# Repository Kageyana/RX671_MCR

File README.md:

# 初期設定
1. ワークスペースのパスは2バイト文字禁止
2. e2studio プロジェクトの設定→C/C++ビルド→設定<br>ツール設定タブ→Compiler→Includesに<br>
```"${workspace_loc:/${ProjName}/inc}"```<br>
を追加
3. Renesas Extensions for Visual Studio Codeを使う場合<br>
	1. 下記ページを参考に拡張機能をインストールする
	https://qiita.com/y_toyoyama/items/98b7511f9f95343f7a40<br>
	2. launch.json<br>
	serverParametersはデバッガ情報をLLMに渡して整形してもらうと楽
	3. CMakeLists.txt<br>
	CMAKE_CURRENT_SOURCE_DIRに```"inc/*.h"```を追加<br>
	CMAKE_CXX_FLAGSにコンパイラオプションを追加する<br>
	CMAKE_EXE_LINKER_FLAGSにリンカオプションを追加する
	4. .clangd<br>
	下記リポジトリを参考に.clangdとc_cpp_intellisense_helper.hを追加する<br>
	https://github.com/NoMaY-jp/Renesas_VSCode_Extensions_tips_for_Renesas_CC_compilers.git

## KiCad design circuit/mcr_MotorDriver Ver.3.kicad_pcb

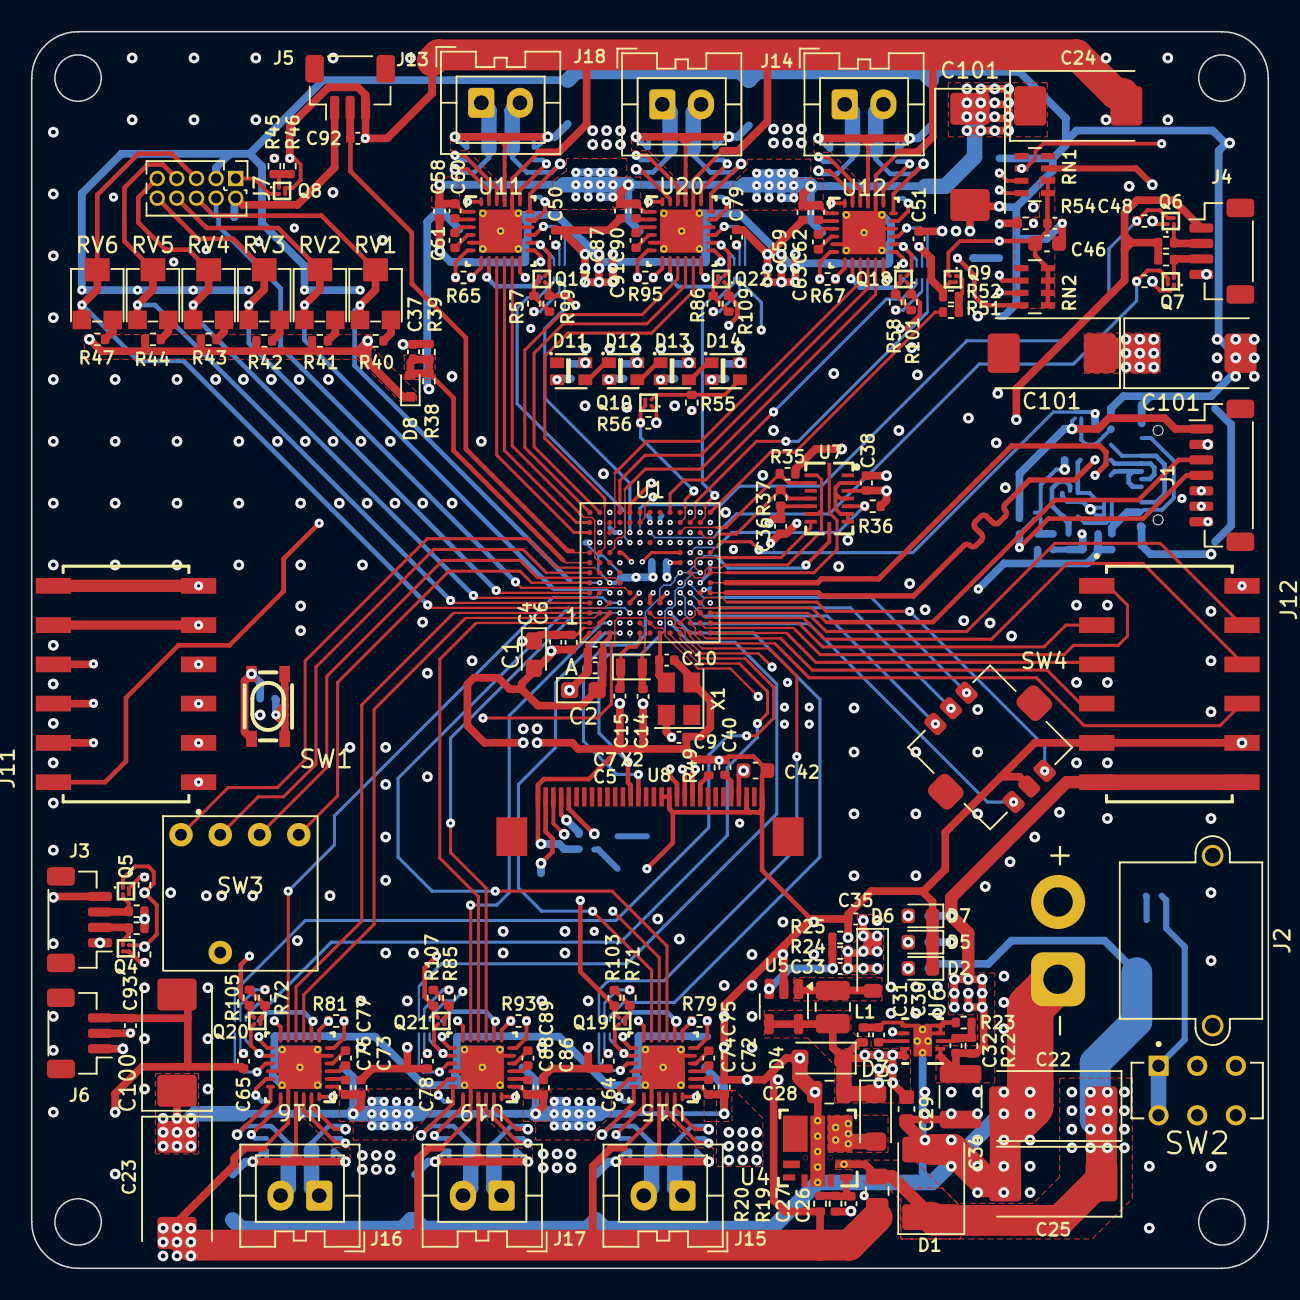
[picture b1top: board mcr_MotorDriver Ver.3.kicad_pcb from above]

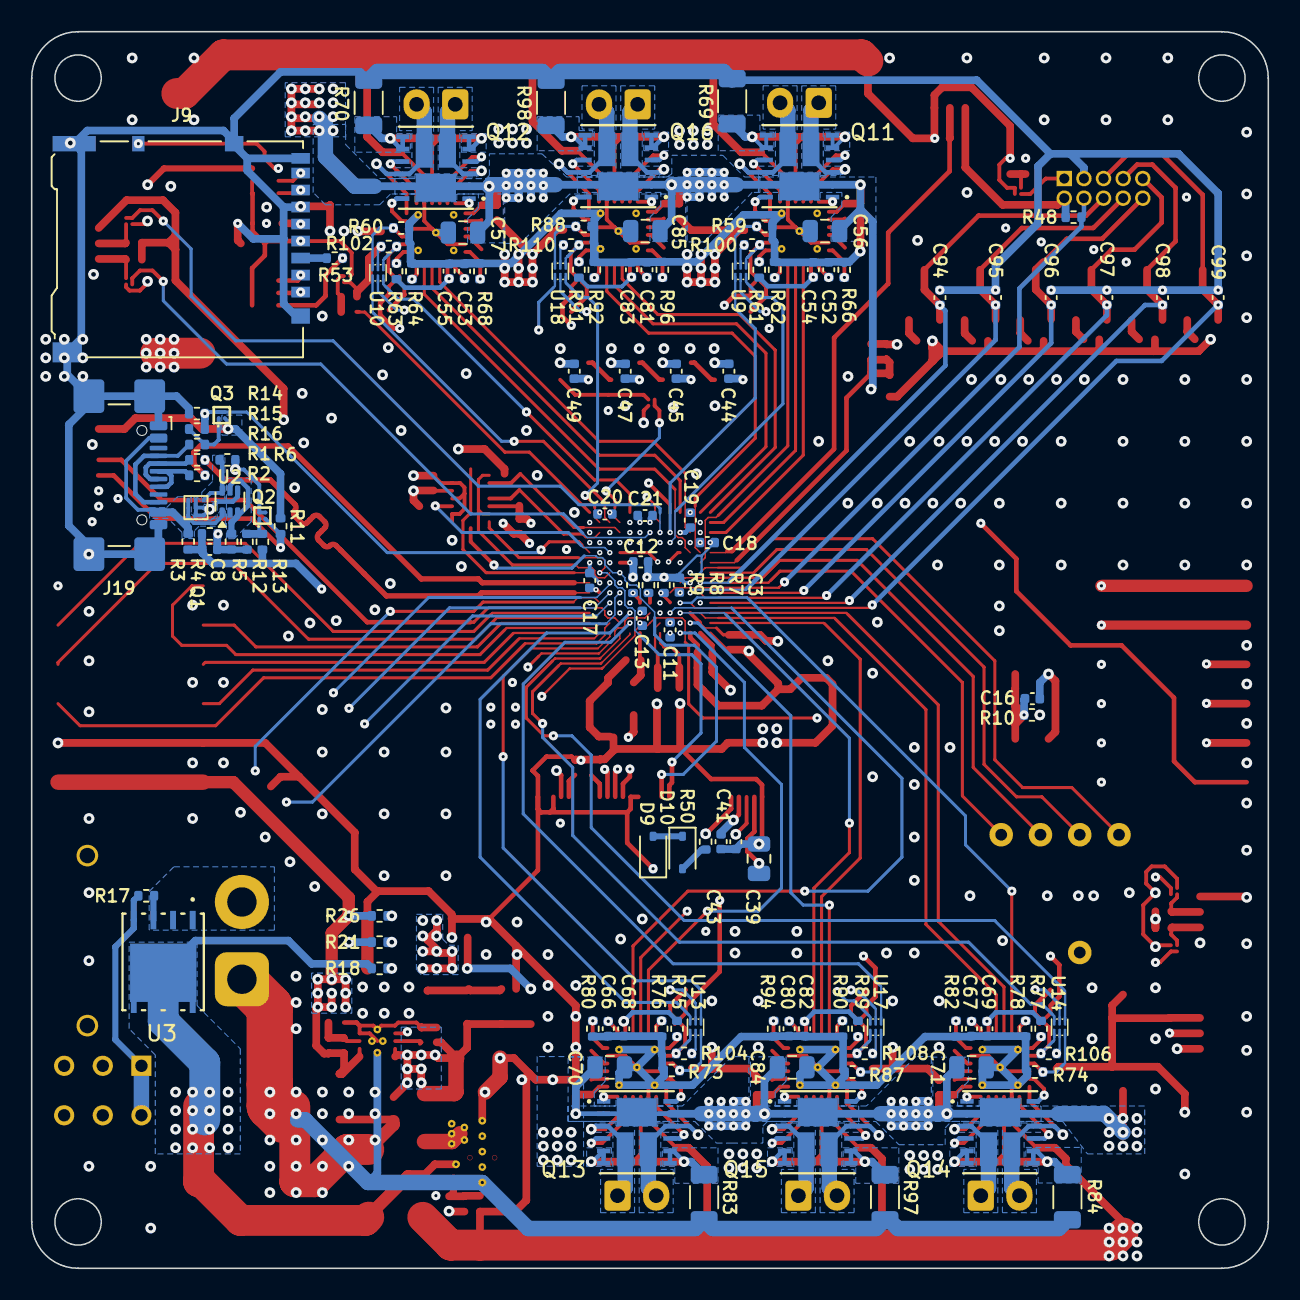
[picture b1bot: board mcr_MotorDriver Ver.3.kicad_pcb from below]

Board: 6 copper layers, 80.0 x 80.0 mm, 301 parts (122 on the bottom side), 268 nets.

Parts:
C1, C2: 10u; CP_EIA-2012-12_Kemet-R
C3, C4, C5, C12, C13, C17, C18, C19, C20, C21, C36, C37, C38, C44, C45, C47, C48, C49, C50, C51, C58, C59, C61, C63, C64, C65, C72, C73, C75, C77, C78, C79, C86, C87, C89, C91: 0.1u; C_0402_1005Metric
C6, C7, C9: 0.01u; C_0402_1005Metric
C8, C40, C41, C43, C52, C53, C54, C55, C60, C62, C66, C67, C68, C69, C74, C76, C80, C81, C82, C83, C88, C90: 1u; C_0402_1005Metric
C10: 15p; C_0402_1005Metric
C11: 0.22u; C_0402_1005Metric
C14, C15, C16: 12p; C_0402_1005Metric
C22, C23, C24, C25, C100, C101, C101#2, C101#3: 150u; CP_EIA-7343-31_Kemet-D
C26, C39, C56, C57, C70, C71, C84, C85: 10u; C_0805_2012Metric
C27: 330p; C_0402_1005Metric
C28: 47u; C_0805_2012Metric
C29, C42, C46: 10u; C_0603_1608Metric
C30: 100n; C_0402_1005Metric
C31: 2.2u; C_0402_1005Metric
C32: 10n; C_0402_1005Metric
C33: 160p; C_0402_1005Metric
C34: 22u; C_1210_3225Metric
C35: 4.7u; C_0402_1005Metric
C92, C93, C94, C95, C96, C97, C98, C99: 1000p; C_0402_1005Metric
D1: 1SMB5931BT3G; D_2114_3652Metric
D2: Red; LED_0603_1608Metric
D3: D_Schottky; D_SOD-123W
D4: KDZVTR6.2B; D_SOD-123F
D5: Yellow; LED_0603_1608Metric
D6: MBR0520; D_SOD-123
D7: Green; LED_0603_1608Metric
D8: BAT30KFILM; D_SOD-523
D9, D10: 1N4148WS; D_SOD-323
D11, D12, D13, D14: WS2812C; WS2812C-2020
J1: SH_01x07; JST_SH_BM07B-SRSS-TB_1x07-1MP_P1.00mm_Vertical
J2: XT30; AMASS_XT30PW-M_1x02_P2.50mm_Horizontal
J3, J4: SH_01x04; JST_SH_BM04B-SRSS-TB_1x04-1MP_P1.00mm_Vertical
J5, J6: SH_01x03; JST_SH_BM03B-SRSS-TB_1x03-1MP_P1.00mm_Vertical
J7: Conn_02x05; FTSH-105-01-F-D-K
J9: Micro_SD_Card_Det_Hirose_DM3AT; microSD_HC_Hirose_DM3AT-SF-PEJM5
J11: Pmod12P_UART; Pmod_2x06_P2.54mm
J12: Pmod12P_SPI; Pmod_2x06_P2.54mm
J13, J14, J15, J16, J17, J18: motor1; JST_XA_B02B-XASK-1_1x02_P2.50mm_Vertical
J19: USB_C_Receptacle_USB2.0_14P; USB_C_Receptacle_GCT_USB4110
L1: 10uH; L_1008_2520Metric
Q1: DMP1011UCB9-7
Q2, Q3, Q4, Q5, Q6, Q7, Q8, Q10, Q17, Q18, Q19, Q20, Q21, Q22: DMN1054UCB4
Q9: DMP1100UCB4-7; DMN1054UCB4
Q11, Q12, Q13, Q14, Q15, Q16: DMHT6016LFJ; V-DFN5045-12_DIO
R1, R2: 27; R_0402_1005Metric
R3: 15k; R_0402_1005Metric
R4, R18: 30k; R_0402_1005Metric
R5, R6: 12.1k; R_0402_1005Metric
R7, R8, R9, R10, R19, R59, R60, R61, R63, R73, R74, R75, R77, R87, R88, R89, R91: 10k; R_0402_1005Metric
R11, R14, R27, R28, R29, R30, R31, R32, R33, R34, R35, R36, R37, R46, R55, R56, R66, R68, R80, R82, R94, R96: 4.7k; R_0402_1005Metric
R12, R15, R17, R52, R99, R100, R101, R102, R103, R104, R105, R106, R107, R108, R109, R110: 47k; R_0402_1005Metric
R13, R16, R45, R51: 330; R_0402_1005Metric
R20: 1.37k; R_0402_1005Metric
R21: 4.6k; R_0402_1005Metric
R22: 3.57k; R_0402_1005Metric
R23: 1.15k; R_0402_1005Metric
R24: 127k; R_0402_1005Metric
R25: 13.3k; R_0402_1005Metric
R26: 800; R_0402_1005Metric
R38: 62k; R_0402_1005Metric
R39: 12k; R_0402_1005Metric
R40, R41, R42, R43, R44, R47, R48: 6.2k; R_0402_1005Metric
R49: 560k; R_0402_1005Metric
R50: 50; R_0402_1005Metric
R53, R54: 22; R_0402_1005Metric
R57, R58, R71, R72, R85, R86: 1k; R_0402_1005Metric
R62, R64, R76, R78, R90, R92: 200k; R_0402_1005Metric
R65, R67, R79, R81, R93, R95: 2.2k; R_0402_1005Metric
R69, R70, R83, R84, R97, R98: 50m; R_1206_3216Metric
RN1, RN2: 22k; R_Array_Concave_4x0603
RV1, RV2, RV3, RV4, RV5, RV6: POT; ST-32EA
SW1: SW_Push; SKRPABE010
SW2: EG1271; SW_EG1271
SW3: FR01FR16P-S
SW4: SKRHAAE010
U1: R5F5671EHGLE; R5F5671EHGLE-20
U2: NSVT3906DXV6T1G; SOT-563
U3: HSBA3119; IRFH7084TRPBF_INF
U4: TPSM84209RKHT
U5: LM2733YMF; SOT-23-5
U6: TPS7A9201DSKR; TPS7A9201DSKT
U7: BMI088
U8: SSD1351
U9, U10, U13, U14, U17, U18: SN74LVC1G18DSFR
U11, U12, U15, U16, U19, U20: DRV8701
X1: OT322516MJBA4SL; Oscillator_SMD_Abracon_ASE-4Pin_3.2x2.5mm
X2: X1A0000610006; Crystal_SMD_2012-2Pin_2.0x1.2mm

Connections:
+3V3: C1.1, C2.1, C3.1, C4.2, C5.2, C6.2, C7.2, C9.1, C12.1, C13.1, C17.1, C18.2, C19.2, C20.1, C21.1, C32.2, C34.2, C36.1, C38.1, C42.2, C43.2, C50.2, C51.2, C64.2, C65.2, C78.2, C79.2, D8.1 (K), J1.1, J5.1, J6.1, J7.2, J11.6, J11.12, J12.6, J12.12, Q3.3 (D), Q4.1 (G), Q5.1 (G), Q6.1 (G), Q7.1 (G), Q9.2 (S), Q10.1 (G), R9.1, R10.2, R11.2, R22.2, R26.2, R27.2, R28.2, R29.2, R30.2, R35.1, R36.2, R37.2, R40.1, R41.1, R42.1, R43.1, R44.1, R47.1, R48.1, R52.2, R56.2, R100.2, R102.2, R104.2, R106.2, R108.2, R110.2, RN1.7 (R2.2), U1.B1 (AVCC1), U1.B2 (AVCC0), U1.B10 (VCC), U1.C3 (VREFH0), U1.D5 (VCC), U1.D11 (VCC), U1.F4 (vbatt), U1.H2 (VCC), U1.H12 (VCC_USB), U1.K8 (VCC), U1.M5 (VCC_USB), U1.M13 (VCC), U6.1 (OUT), U6.2 (OUT), U7.3 (VDD), U7.11 (VDDIO), U8.4 (VDDIO), U8.27 (VCI), U9.5 (Vcc), U10.5 (Vcc), U13.5 (Vcc), U14.5 (Vcc), U17.5 (Vcc), U18.5 (Vcc), X1.4 (Vdd)
+5V: C27.2, C28.2, C29.2, C31.2, C44.2, C45.2, C47.2, C49.2, D3.1 (K), D4.1 (K), D11.4 (VDD), D12.4 (VDD), D13.4 (VDD), D14.4 (VDD), J3.1, J4.1, L1.1, Q1.2 (S), R19.2, R21.2, R31.2, R32.2, R33.2, R34.2, R55.2, U2.4 (E1), U5.4 (EN), U5.5 (VIN), U6.7 (EN), U6.9 (IN), U6.10 (IN)
+13V: C33.2, C35.2, C39.2, D6.1 (K), R24.2, U8.2 (VCC)
+BATT: C22.1, C23.1, C24.1, C25.1, C26.2, C56.1, C57.1, C58.1, C59.1, C60.1, C62.1, C70.1, C71.1, C72.1, C73.1, C74.1, C76.1, C84.1, C85.1, C86.1, C87.1, C88.1, C90.1, C100.1, C101.1, C101#2.1, C101#3.1, D1.1 (K), Q11.2 (D1/D4), Q11.11 (D1/D4), Q11.13 (D1/D4), Q12.2 (D1/D4), Q12.11 (D1/D4), Q12.13 (D1/D4), Q13.2 (D1/D4), Q13.11 (D1/D4), Q13.13 (D1/D4), Q14.2 (D1/D4), Q14.11 (D1/D4), Q14.13 (D1/D4), Q15.2 (D1/D4), Q15.11 (D1/D4), Q15.13 (D1/D4), Q16.2 (D1/D4), Q16.11 (D1/D4), Q16.13 (D1/D4), R18.2, R38.2, U3.5 (D), U3.6 (D), U3.7 (D), U3.8 (D), U4.2 (VIN), U11.1 (VM), U12.1 (VM), U15.1 (VM), U16.1 (VM), U19.1 (VM), U20.1 (VM)
/MCU/AN001: C99.2, J7.5, RV6.2, RV6.3, U1.C4 (P41)
/MCU/AN002: C98.2, J7.7, RV5.2, RV5.3, U1.A4 (P42)
/MCU/AN003: C97.2, J7.9, RV4.2, RV4.3, U1.B5 (P43)
/MCU/AN004: J7.4, R48.2, U1.E5 (P44)
/MCU/AN005: C96.2, J7.10, RV3.2, RV3.3, U1.A5 (P45)
/MCU/AN006: C95.2, J7.8, RV2.2, RV2.3, U1.C5 (P46)
/MCU/AN007: C94.2, J7.6, RV1.2, RV1.3, U1.B6 (P47)
/MCU/AN100: U1.C9 (PD7), U12.11 (SO)
/MCU/AN101: C92.2, J5.2, U1.A9 (PD6)
/MCU/AN103: U1.B9 (PD4), U20.11 (SO)
/MCU/AN105: C37.2, D8.2 (A), R38.1, R39.2, U1.A8 (PD2)
/MCU/AN106: C93.2, J6.2, U1.C7 (PD1)
/MCU/AN107: U1.B8 (PD0), U11.11 (SO)
/MCU/AN109: U1.C2 (P02), U19.11 (SO)
/MCU/AN110: U1.D4 (P01), U16.11 (SO)
/MCU/AN111: U1.D1 (P00), U15.11 (SO)
/MCU/EXTAL: C10.2, U1.H1 (EXTAL), X1.3 (OUT)
/MCU/IRQ10: U1.N7 (P55), U7.16 (INT1)
/MCU/IRQ14: R37.1, U1.M11 (PC0), U7.12 (INT3)
/MCU/MD: J1.4, Q2.3 (D), R11.1, U1.G3 (md/fined)
/MCU/MTIOC0A: U1.J1 (P34), U14.3 (A)
/MCU/MTIOC0C: U1.J3 (P32), U13.3 (A)
/MCU/MTIOC3A: U1.M12 (PC1), U18.3 (A)
/MCU/MTIOC3C: U1.F3 (pj3), U17.3 (A)
/MCU/MTIOC4A: U1.E10 (PA0), U9.3 (A)
/MCU/MTIOC4C: U1.J13 (PB1), U10.3 (A)
/MCU/MTIOC7C: R45.1, U1.E13 (P67)
/MCU/MTLCKA: Q6.2 (S), R29.1, U1.F11 (PA4)
/MCU/MTLCKB: Q7.2 (S), R30.1, U1.G11 (PA6)
/MCU/MTLCKC: Q5.2 (S), R28.1, U1.F12 (PA1)
/MCU/MTLCKD: Q4.2 (S), R27.1, U1.F10 (PA3)
/MCU/P03: U1.D3 (P03), U19.9 (FAULT_N)
/MCU/P05: U1.B3 (P05), U16.9 (FAULT_N)
/MCU/P07: U1.A2 (P07), U19.10 (SNSOUT)
/MCU/P12: SW4.4, U1.M4 (P12)
/MCU/P13: SW4.2, U1.L5 (P13)
/MCU/P14: Q21.1 (G), R107.1, U1.N4 (P14)
/MCU/P15: Q20.1 (G), R105.1, U1.K4 (P15)
/MCU/P17(CS): J12.1, U1.M2 (P17)
/MCU/P20(MOSI): J12.2, U1.N2 (P20)
/MCU/P21(MISO): J12.3, U1.N1 (P21)
/MCU/P22(SCK): J12.4, U1.M1 (P22)
/MCU/P23: J12.10, U1.L2 (P23)
/MCU/P24: SW4.3, U1.L4 (P24)
/MCU/P25: U1.L1 (P25), U13.1 (S)
/MCU/P27: U1.K1 (P27), U14.1 (S)
/MCU/P31(INT): J12.7, U1.K3 (P31)
/MCU/P33: U1.J2 (P33), U17.1 (S)
/MCU/P40: U1.A3 (P40), U16.10 (SNSOUT)
/MCU/P53: U1.K6 (P53*1), U8.21 (RES#)
/MCU/P54: SW4.6, U1.K5 (P54)
/MCU/P56: SW4.1, U1.L6 (P56)
/MCU/P60: U1.D8 (P60), U8.19 (CS#)
/MCU/P61: J11.10, U1.B11 (P61)
/MCU/P62: U1.A11 (P62), U11.9 (FAULT_N)
/MCU/P63: J11.9, U1.C10 (P63)
/MCU/P64: U1.D9 (P64), U8.20 (D/C#)
/MCU/P66: U1.E11 (P66), U9.1 (S)
/MCU/P73: U1.L12 (P73), U10.1 (S)
/MCU/P74: R51.2, U1.N13 (P74)
/MCU/P80(RTS): J11.4, U1.K9 (P80)
/MCU/P82(TXD): J11.2, U1.N10 (P82)
/MCU/P83(CTS): J11.1, U1.L8 (P83)
/MCU/P86: J12.9, U1.M3 (P86)
/MCU/P87(RESET): J12.8, U1.N3 (P87)
/MCU/P90: SW3.8, U1.A6 (P90)
/MCU/P91: SW3.1, U1.B7 (P91)
/MCU/P92: SW3.2, U1.A7 (P92)
/MCU/P93: SW3.4, U1.D6 (P93)
/MCU/PA7: Q17.1 (G), R99.1, U1.H11 (PA7)
/MCU/PB0: U1.H10 (PB0), U18.1 (S)
/MCU/PB2: Q22.1 (G), R109.1, U1.J12 (PB2)
/MCU/PB3: Q19.1 (G), R103.1, U1.J10 (PB3)
/MCU/PB4: Q18.1 (G), R101.1, U1.J11 (PB4)
/MCU/PB7: R35.2, U1.K11 (PB7), U7.14 (CSB1)
/MCU/PC5: R36.1, U1.L9 (PC5), U7.5 (CSB2)
/MCU/PC6(RXD): J11.3, U1.M8 (PC6)
/MCU/PE0: U1.C11 (PE0), U12.9 (FAULT_N)
/MCU/PE1: U1.A12 (PE1), U11.10 (SNSOUT)
/MCU/PE2(INT): J11.7, U1.B12 (PE2)
/MCU/PE3: U1.A13 (PE3), U20.9 (FAULT_N)
/MCU/PE4: U1.B13 (PE4), U20.10 (SNSOUT)
/MCU/PE6: U1.D13 (PE6), U12.10 (SNSOUT)
/MCU/PE7: J11.8, U1.D10 (PE7)
/MCU/PF5: U1.D2 (PF5), U15.10 (SNSOUT)
/MCU/Pj5: U1.E3 (PJ5), U15.9 (FAULT_N)
/MCU/RXD1: J1.5, U1.J4 (P30)
/MCU/Reset: C16.2, J1.6, R10.1, SW1.2, U1.G2 (res#)
/MCU/SDHI_CD: J9.10 (DET_A), RN1.2 (R2.1), U1.M9 (P81)
/MCU/SDHI_CLK: R54.2, U1.M10 (P77)
/MCU/SDHI_CMD: R53.2, RN2.4 (R4.1), U1.K10 (P76)
/MCU/SDHI_D0: J9.7 (DAT0), RN1.4 (R4.1), U1.N11 (PC3)
/MCU/SDHI_D1: J9.8 (DAT1), RN1.3 (R3.1), U1.L10 (PC4)
/MCU/SDHI_D2: J9.1 (DAT2), RN2.3 (R3.1), U1.N12 (P75)
/MCU/SDHI_D3: J9.2 (DAT3/CD), RN2.2 (R2.1), U1.L11 (PC2)
/MCU/TIOCA5: Q10.2 (S), R56.1, U1.K12 (PB6)
/MCU/TXD1: J1.3, U1.K2 (P26)
/MCU/UB: J1.7, Q3.2 (S), R14.2, R15.1, U1.N9 (PC7)
/MCU/USB0_D+: R2.2, U1.N6 (USB0_DP)
/MCU/USB0_D-: R1.2, U1.N5 (USB0_DM)
/MCU/USB0_VBUS: C8.2, R3.2, R4.2, R13.2, U1.L3 (P16)
/MCU/xcin: C15.1, U1.F1 (xcin), X2.1
/MCU/xcout: C14.1, U1.F2 (xcout), X2.2
/MISO: U1.L7 (P52), U7.10 (SDO2), U7.15 (SDO1)
/MOSI: U1.M7 (P50), U7.9 (SDI), U8.13 (D1)
/SCK: U1.K7 (P51), U7.8 (SCK), U8.14 (D0)
CC: J19.A5 (CC1), J19.B5 (CC2), R16.2
GND: C1.2, C2.2, C3.2, C4.1, C5.1, C6.1, C7.1, C8.1, C9.2, C10.1, C11.2, C12.2, C13.2, C14.2, C15.2, C16.1, C17.2, C18.1, C19.1, C20.2, C21.2, C22.2, C23.2, C24.2, C25.2, C26.1, C28.1, C29.1, C30.1, C31.1, C34.1, C35.1, C36.2, C37.1, C38.2, C39.1, C40.1, C41.1, C42.1, C43.1, C44.1, C45.1, C46.2, C47.1, C48.2, C49.1, C50.1, C51.1, C52.2, C53.2, C54.2, C55.2, C56.2, C57.2, C58.2, C59.2, C64.1, C65.1, C66.2, C67.2, C68.2, C69.2, C70.2, C71.2, C72.2, C73.2, C78.1, C79.1, C80.2, C81.2, C82.2, C83.2, C84.2, C85.2, C86.2, C87.2, C92.1, C93.1, C94.1, C95.1, C96.1, C97.1, C98.1, C99.1, C100.2, C101.2, C101#2.2, C101#3.2, D1.2 (A), D2.1 (K), D4.2 (A), D5.1 (K), D7.1 (K), D9.1 (K), D11.2 (VSS), D12.2 (VSS), D13.2 (VSS), D14.2 (VSS), J1.2, J2.1, J3.4, J4.4, J5.3, J6.3, J7.3, J9.6 (VSS), J9.9 (DET_B), J9.11 (SHIELD), J11.5, J11.11, J12.5, J12.11, J19.A1 (GND), J19.A12 (GND), J19.B1 (GND), J19.B12 (GND), J19.S1 (SHIELD), Q2.2 (S), Q8.2 (S), R4.1, R5.1, R6.1, R7.2, R8.2, R12.1, R14.1, R20.1, R23.1, R25.1, R39.1, R46.1, R49.1, R57.1, R58.1, R59.1, R60.1, R62.1, R64.1, R66.1, R68.1, R69.1, R70.1, R71.1, R72.1, R73.1, R74.1, R76.1, R78.1, R80.1, R82.1, R83.1, R84.1, R85.1, R86.1, R87.1, R88.1, R90.1, R92.1, R94.1, R96.1, R97.1, R98.1, SW1.1, SW2.2, SW2.5, SW3.C, SW4.5, U1.A1 (AVSS0), U1.A10 (VSS), U1.B4 (VREFL0), U1.C1 (AVSS1), U1.C6 (VSS), U1.C13 (VSS), U1.E1 (VSS), U1.G12 (VSS_USB), U1.H3 (VSS), U1.L13 (VSS), U1.M6 (VSS_USB), U1.N8 (VSS), U4.8 (GND), U5.2 (GND), U6.4 (GND), U6.5 (PG), U6.6 (SS_CTRL), U6.11 (PAD), U7.2 (NC), U7.4 (GND), U7.6 (GNDIO), U7.7 (PS), U8.1 (NC(GND)), U8.17 (BS0), U8.18 (BS1), U8.28 (VSS), U8.30 (NC(GND)), U9.2 (GND), U10.2 (GND), U11.5 (GND), U11.16 (GND), U11.20 (SN), U11.25 (PAD), U12.5 (GND), U12.16 (GND), U12.20 (SN), U12.25 (PAD), U13.2 (GND), U14.2 (GND), U15.5 (GND), U15.16 (GND), U15.20 (SN), U15.25 (PAD), U16.5 (GND), U16.16 (GND), U16.20 (SN), U16.25 (PAD), U17.2 (GND), U18.2 (GND), U19.5 (GND), U19.16 (GND), U19.20 (SN), U19.25 (PAD), U20.5 (GND), U20.16 (GND), U20.20 (SN), U20.25 (PAD), X1.2 (GND)
unnamed: D2.2 (A), R18.1
unnamed: D3.2 (A), U4.3 (VOUT)
unnamed: D5.2 (A), R21.1
unnamed: D6.2 (A), L1.2, U5.1 (SW)
unnamed: D7.2 (A), R26.1
unnamed: D10.2 (A), R50.1
unnamed: D9.2 (A), D10.1 (K)
unnamed: D11.3 (DIN), D12.1 (DOUT)
unnamed: D12.3 (DIN), D13.1 (DOUT)
unnamed: D13.3 (DIN), D14.1 (DOUT)
unnamed: D14.3 (DIN), Q10.3 (D), R55.1
unnamed: J2.2, R17.2, U3.1 (S), U3.2 (S), U3.3 (S)
unnamed: J3.2, Q4.3 (D), R33.1
unnamed: J3.3, Q5.3 (D), R31.1
unnamed: J4.2, Q6.3 (D), R34.1
unnamed: J4.3, Q7.3 (D), R32.1
unnamed: J7.1, Q8.3 (D)
unnamed: J9.5 (CLK), R54.1
unnamed: J9.3 (CMD), R53.1
unnamed: C46.1, C48.1, J9.4 (VDD), Q9.3 (D), RN1.5 (R4.2), RN1.6 (R3.2), RN2.5 (R4.2), RN2.6 (R3.2), RN2.7 (R2.2), RN2.8 (R1.2)
unnamed: J13.1, Q11.3 (S1/D2), Q11.14 (S1/D2), U11.23 (SH2)
unnamed: J13.2, Q11.10 (D4/D3), Q11.15 (D4/D3), U11.18 (SH1)
unnamed: J14.1, Q12.3 (S1/D2), Q12.14 (S1/D2), U12.23 (SH2)
unnamed: J14.2, Q12.10 (D4/D3), Q12.15 (D4/D3), U12.18 (SH1)
unnamed: J15.1, Q13.3 (S1/D2), Q13.14 (S1/D2), U15.23 (SH2)
unnamed: J15.2, Q13.10 (D4/D3), Q13.15 (D4/D3), U15.18 (SH1)
unnamed: J16.1, Q14.3 (S1/D2), Q14.14 (S1/D2), U16.23 (SH2)
unnamed: J16.2, Q14.10 (D4/D3), Q14.15 (D4/D3), U16.18 (SH1)
unnamed: J17.1, Q15.3 (S1/D2), Q15.14 (S1/D2), U19.23 (SH2)
unnamed: J17.2, Q15.10 (D4/D3), Q15.15 (D4/D3), U19.18 (SH1)
unnamed: J18.1, Q16.3 (S1/D2), Q16.14 (S1/D2), U20.23 (SH2)
unnamed: J18.2, Q16.10 (D4/D3), Q16.15 (D4/D3), U20.18 (SH1)
unnamed: J19.A6 (D+), J19.B6 (D+), R2.1
unnamed: J19.A7 (D-), J19.B7 (D-), R1.1
unnamed: J19.A4 (VBUS), J19.A9 (VBUS), J19.B4 (VBUS), J19.B9 (VBUS), Q1.3 (D), R3.1, U2.1 (E2)
unnamed: Q1.1 (G), R6.2, U2.6 (C2)
unnamed: Q2.1 (G), R12.2, R13.1
unnamed: Q3.1 (G), R15.2, R16.1
unnamed: Q8.1 (G), R45.2, R46.2
unnamed: Q9.1 (G), R51.1, R52.1
unnamed: Q11.1 (G1), U11.24 (GH2)
unnamed: Q11.4 (G2), U11.22 (GL2)
unnamed: Q11.9 (G3), U11.19 (GL1)
unnamed: Q11.12 (G4), U11.17 (GH1)
unnamed: Q12.1 (G1), U12.24 (GH2)
unnamed: Q12.4 (G2), U12.22 (GL2)
unnamed: Q12.9 (G3), U12.19 (GL1)
unnamed: Q12.12 (G4), U12.17 (GH1)
unnamed: Q13.1 (G1), U15.24 (GH2)
unnamed: Q13.4 (G2), U15.22 (GL2)
unnamed: Q13.9 (G3), U15.19 (GL1)
unnamed: Q13.12 (G4), U15.17 (GH1)
unnamed: Q14.1 (G1), U16.24 (GH2)
unnamed: Q14.4 (G2), U16.22 (GL2)
unnamed: Q14.9 (G3), U16.19 (GL1)
unnamed: Q14.12 (G4), U16.17 (GH1)
unnamed: Q15.1 (G1), U19.24 (GH2)
unnamed: Q15.4 (G2), U19.22 (GL2)
unnamed: Q15.9 (G3), U19.19 (GL1)
unnamed: Q15.12 (G4), U19.17 (GH1)
unnamed: Q16.1 (G1), U20.24 (GH2)
unnamed: Q16.4 (G2), U20.22 (GL2)
unnamed: Q16.9 (G3), U20.19 (GL1)
unnamed: Q16.12 (G4), U20.17 (GH1)
unnamed: Q17.3 (D), R100.1, U9.4 (Y1), U11.14 (EN_IN2)
unnamed: Q17.2 (S), R57.2, R99.2
unnamed: Q18.3 (D), R102.1, U10.4 (Y1), U12.14 (EN_IN2)
unnamed: Q18.2 (S), R58.2, R101.2
unnamed: Q19.3 (D), R104.1, U13.4 (Y1), U15.14 (EN_IN2)
unnamed: Q19.2 (S), R71.2, R103.2
unnamed: Q20.3 (D), R106.1, U14.4 (Y1), U16.14 (EN_IN2)
unnamed: Q20.2 (S), R72.2, R105.2
unnamed: Q21.3 (D), R108.1, U17.4 (Y1), U19.14 (EN_IN2)
unnamed: Q21.2 (S), R85.2, R107.2
unnamed: Q22.3 (D), R110.1, U18.4 (Y1), U20.14 (EN_IN2)
unnamed: Q22.2 (S), R86.2, R109.2
unnamed: R40.2, RV1.1
unnamed: R41.2, RV2.1
unnamed: R42.2, RV3.1
unnamed: R43.2, RV4.1
unnamed: R44.2, RV5.1
unnamed: R47.2, RV6.1
unnamed: R8.1, U1.G4 (BSCANP)
unnamed: R7.1, U1.E4 (EMLE)
unnamed: R9.2, U1.H4 (P35)
unnamed: C11.1, U1.E2 (VCL)
unnamed: R5.2, U2.2 (B2), U2.3 (C1), U2.5 (B1)
unnamed: R17.1, SW2.1, SW2.4, U3.4 (G)
unnamed: C27.1, R19.1, R20.2, U4.1 (FB)
unnamed: C33.1, R24.1, R25.2, U5.3 (FB)
unnamed: C32.1, R22.1, R23.2, U6.3 (FB)
unnamed: C30.2, U6.8 (NR_SS)
unnamed: R49.2, U8.22 (IREF)
unnamed: C41.2, U8.3 (VCOMH)
unnamed: C40.2, U8.26 (VDD)
unnamed: R50.2, U8.5 (VSL)
unnamed: R60.2, U10.6 (Y0), U12.15 (PH_IN1)
unnamed: C52.1, R65.2, U11.7 (AVDD)
unnamed: C61.1, U11.3 (CPH)
unnamed: C61.2, U11.4 (CPL)
unnamed: C54.1, R61.2, U11.8 (DVDD)
unnamed: R62.2, U11.12 (IDRIVE)
unnamed: R59.2, U9.6 (Y0), U11.15 (PH_IN1)
unnamed: R61.1, U11.13 (SLEEP_N)
unnamed: Q11.5 (S2), Q11.6 (S2), Q11.7 (S3), Q11.8 (S3), R69.2, U11.21 (SP)
unnamed: C60.2, U11.2 (VCP)
unnamed: R65.1, R66.2, U11.6 (VREF)
unnamed: C53.1, R67.2, U12.7 (AVDD)
unnamed: C63.1, U12.3 (CPH)
unnamed: C63.2, U12.4 (CPL)
unnamed: C55.1, R63.2, U12.8 (DVDD)
unnamed: R64.2, U12.12 (IDRIVE)
unnamed: R63.1, U12.13 (SLEEP_N)
unnamed: Q12.5 (S2), Q12.6 (S2), Q12.7 (S3), Q12.8 (S3), R70.2, U12.21 (SP)
unnamed: C62.2, U12.2 (VCP)
unnamed: R67.1, R68.2, U12.6 (VREF)
unnamed: R73.2, U13.6 (Y0), U15.15 (PH_IN1)
unnamed: R74.2, U14.6 (Y0), U16.15 (PH_IN1)
unnamed: C66.1, R79.2, U15.7 (AVDD)
unnamed: C75.1, U15.3 (CPH)
unnamed: C75.2, U15.4 (CPL)
unnamed: C68.1, R75.2, U15.8 (DVDD)
unnamed: R76.2, U15.12 (IDRIVE)
unnamed: R75.1, U15.13 (SLEEP_N)
unnamed: Q13.5 (S2), Q13.6 (S2), Q13.7 (S3), Q13.8 (S3), R83.2, U15.21 (SP)
unnamed: C74.2, U15.2 (VCP)
unnamed: R79.1, R80.2, U15.6 (VREF)
unnamed: C67.1, R81.2, U16.7 (AVDD)
unnamed: C77.1, U16.3 (CPH)
unnamed: C77.2, U16.4 (CPL)
unnamed: C69.1, R77.2, U16.8 (DVDD)
unnamed: R78.2, U16.12 (IDRIVE)
unnamed: R77.1, U16.13 (SLEEP_N)
unnamed: Q14.5 (S2), Q14.6 (S2), Q14.7 (S3), Q14.8 (S3), R84.2, U16.21 (SP)
unnamed: C76.2, U16.2 (VCP)
unnamed: R81.1, R82.2, U16.6 (VREF)
unnamed: R87.2, U17.6 (Y0), U19.15 (PH_IN1)
unnamed: R88.2, U18.6 (Y0), U20.15 (PH_IN1)
unnamed: C80.1, R93.2, U19.7 (AVDD)
unnamed: C89.1, U19.3 (CPH)
unnamed: C89.2, U19.4 (CPL)
unnamed: C82.1, R89.2, U19.8 (DVDD)
unnamed: R90.2, U19.12 (IDRIVE)
unnamed: R89.1, U19.13 (SLEEP_N)
unnamed: Q15.5 (S2), Q15.6 (S2), Q15.7 (S3), Q15.8 (S3), R97.2, U19.21 (SP)
unnamed: C88.2, U19.2 (VCP)
unnamed: R93.1, R94.2, U19.6 (VREF)
unnamed: C81.1, R95.2, U20.7 (AVDD)
unnamed: C91.1, U20.3 (CPH)
unnamed: C91.2, U20.4 (CPL)
unnamed: C83.1, R91.2, U20.8 (DVDD)
unnamed: R92.2, U20.12 (IDRIVE)
unnamed: R91.1, U20.13 (SLEEP_N)
unnamed: Q16.5 (S2), Q16.6 (S2), Q16.7 (S3), Q16.8 (S3), R98.2, U20.21 (SP)
unnamed: C90.2, U20.2 (VCP)
unnamed: R95.1, R96.2, U20.6 (VREF)

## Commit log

2025-03-22 init
2025-04-10 SSD1351のテスト（表示できない）
2025-04-12 SSD1351動作確認 SPIの一回の送信量を1024byteに制限
2025-04-13 ssd1351用のprintfを実装
2025-04-13 BMI088の読み込みできた 数値は不安定
2025-04-14 BMI088の読み込み完了 角速度正常に読み取りできた
2025-04-19 SSD1306のライブラリをSSD1351に変換中
2025-04-19 表示データをバッファに保存して一括で送信するようにした
2025-04-19 文字列の表示ができた
2025-04-27 SSD1351送信関数を数行ずつに分けて送信するように変更
2025-04-29 e2Studioに移行
2025-04-30 Renesas Extensions for Visual Studio Codeを試す(動いてない)
2025-04-30 Renesas Extensions for Visual Studio Codeでビルドできた(デバッグはできない)
2025-05-01 デバッグできた
2025-05-01 RX671/R671フォルダ.gitファイルを追加した
2025-05-01 RX671/R671フォルダ.gitファイルを追加した(git_dirを変更)
2025-05-01 RX671/R671フォルダ.gitファイルを追加
2025-05-02 printf時に色が反転する問題を修正
2025-05-02 関数名をローワーキャメルケースに変更した
2025-05-05 ディスプレイバッファの前回値比較をmemcpyに変更
2025-05-08 リポジトリ構造変更
2025-05-10 clangdファイル変更
2025-05-10 README更新
2025-05-10 IMUで加速度、温度の取得ができた IMUキャリブレーションができた
2025-05-11 相補フィルターでピッチ、ロール角度の補正をする(math.hをインクルードできなくて動いてない)
2025-05-11 math.hをインクルードできた 相補フィルターも動いた
2025-05-11 意図しないピクセル描画問題を修正した ダミー受信アドレスとバッファアドレスが被っていたのでバッファ変数にstatic修飾追加
2025-05-11 WS2812Cの動作関数を実装 動かない
2025-05-11 fill関数のカラーが反転する問題を修正
2025-05-12 5方向タクトスイッチとロータリスイッチが使えた
2025-05-21 SDHIを使用したFATファイルシステムでの読み書きができた
2025-05-21 f_printfとf_getsが使えた
2025-05-21 SSD1351とIMUの動作を統合
2025-05-24 SDカード関数を外部ファイルに移動
2025-05-24 sdWorkareaをグローバル変数にしてFatfsのエラー解消
2025-05-25 DMAをFITモジュールに変更
2025-05-25 FatFs+DMAテスト中
2025-05-25 FatFs+DMAが動いた
2025-05-25 IMUのログ取得ができた
2025-05-25 SDカードの電源待ち時間を短縮
2025-05-25 位相係数モードが動いた
2025-05-25 位相計数モードを外部ファイル化
2025-05-26 モータ動かそうとしたけど動かない
2025-05-26 QRコードの表示できた
2025-05-26 SSD1351のコントラスト調整を関数化
2025-05-29 AD変換の取得ができた
2025-06-02 PNGのチャンク読み取り機能追加(画像データの解凍は未実装)
2025-06-02 SDカード挿抜割り込みを有効にした
2025-06-04 Fix motor current macros
2025-06-04 Fix battery function name
2025-06-04 Fix header guards
2025-06-05 Remove blank lines after function closing braces
2025-06-07 Remove menu loop from main
2025-06-07 Wrap menu navigation
2025-06-07 Combine AD read and voltage calc
2025-06-07 Call status bar update at cnt10=4
2025-06-07 バッテリ電圧を正しく表示できた
2025-06-07 Update menu function comments
2025-06-07 GUI_MenuSelect内のループを削除
2025-06-07 Use tabs for line_buffer union
2025-06-08 メインループ中で黒帯が出る現象を修正
2025-06-08 Fix indentation to tabs
2025-06-08 2ページ目を追加
2025-06-08 Restore status bar updates and fix indentation
2025-06-08 コントラスト調整中に処理が止まる現象を修正
2025-06-08 Add separate RGB contrast adjustment with test pattern
2025-06-08 コントラスト調整機能の操作性向上
2025-06-09 ディスプレイの色反転機能を追加
2025-06-09 QRコード表示機能を追加
2025-06-10 Add sensor page for rotary switch 0x2
2025-06-10 Add init check in calcDegrees and call unconditionally
2025-06-11 Add comments to sensor display function
2025-06-11 Add sensor page clear initialization
2025-06-11 Clear display on page change
2025-06-11 インデント調整
2025-06-14 Fix sensor page initialization
2025-06-14 Remove unused sensor reset
2025-06-14 Add sensor selection menus
2025-06-14 Improve sensor menu and add reset
2025-06-14 Remove sensor page reset and show IMU info together
2025-06-14 Show IMU axes labels
2025-06-14 Display IMU axes on separate lines
2025-07-06 モーターが回った
2025-07-06 ラインセンサが動いた(タイマ割り込み、連続スキャンモード)
2025-07-16 スマコンの設定変更 回路図変更
2025-07-16 スマコンのコード生成完了
2025-07-29 一時保存
2025-07-30 右後輪以外回った
2025-07-31 自動生成関数を編集しないでも5ポート回せるようにした
2025-08-01 Move menu data into Setup module
2025-08-01 コードを整理
2025-08-04 Move MAX_MENU_STATE definition to header
2025-08-05 Display motor current on sensor page
2025-08-05 Display motor run state and duty percent
2025-08-05 コード整理
2025-08-05 Move sensor menu init flag to function
2025-08-05 センサページ遷移時にボタン状態が残って停止する問題を修正
2025-08-05 バッテリの表示を整数型に変更(浮動小数点表示するとフリーズする)
2025-08-05 Use bounded buffer for SSD1351printf
2025-08-06 Implement lightweight float formatting for SSD1351
2025-08-06 doc: add overview comments for float helpers
2025-08-06 Handle field width in SSD1351printf
2025-08-06 add comments to GUI_ShowSensors
2025-08-06 Pad float width to include fractional part
2025-08-06 コメントを整理
2025-08-06 Interpret %f width as total field width
2025-08-06 コメント修正
2025-08-06 自動生成ファイルを無視
2025-08-06 gitignore反映
2025-08-06 robotrace_v2からcontrol.h emergencyStop.hのフォーマットを移植
2025-08-06 ラインセンサ値の表示を見やすく修正
2025-08-06 センサページにポテンションメータを追加
2025-08-06 docs: describe PID tuning workflows
2025-08-07 feat: color PID output when running
2025-08-07 出力時にラインセンサを起動するようにした
2025-08-07 表示位置を修正
2025-08-09 SDかうどにかきこみ
2025-08-09 スタート部分を実装
2025-08-09 Start page selections set run modes
2025-08-09 通常トレースまで実装
2025-08-10 1周完走した
2025-08-11 reRo杯で1周走った
2025-08-13 fix: correct start extern declaration
2025-08-13 Fix BMI088 header include case
2025-08-13 fix: update include guard for PIDcontrol
2025-08-13 Rename pulse constants
2025-08-13 Add counter increment and delay during SD card detection
2025-08-13 Fix battery voltage divider to use float
2025-08-13 カーブ中のデフ関数を実装
2025-08-13 センサ全灯、消灯時の緊急停止を追加
2025-08-16 RGBLEDが光った
2025-08-16 RGBLED用のTPU5をSCI9に変更
2025-08-17 refactor: remove redundant fullColorLED initialization
2025-08-17 モータドライバピンを入れ替え
2025-08-17 fix: LEDを右端から順に色変化
2025-08-17 refactor: 右端から順に色が変わるLED制御を統合
2025-08-17 fix: pattern 初期化を2個飛ばしに変更
2025-09-12 ピン設定更新
